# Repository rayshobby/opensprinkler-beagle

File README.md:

opensprinkler-beagle
====================

OpenSprinkler Beagle (http://beagle.opensprinkler.com)

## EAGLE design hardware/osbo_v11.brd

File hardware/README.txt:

OpenSprinkler Beagle (OSBo) Eagle Design Files
==========================================
Note: requires Eagle CAD v6.0 or above

Part lists of all versions can be found at:
http://xxx

Release Notes
=============
Version 1.1
---------------------
- Changed to use OpenSprinkler injection-molded enclosure
- Changed relay to HK4100F-5V

Initial Release v1.0
---------------------
- LM2596S-5.0 switching regulator.
- DS1307 RTC with CR1220 backup battery.
- Shift register, BT1308W triac solenoid driver.
- SMBJ48CA bidirectional TVS.
- 5V mini-relay (contact rating 120VAC/2A).
- 2A solder-on fuse.

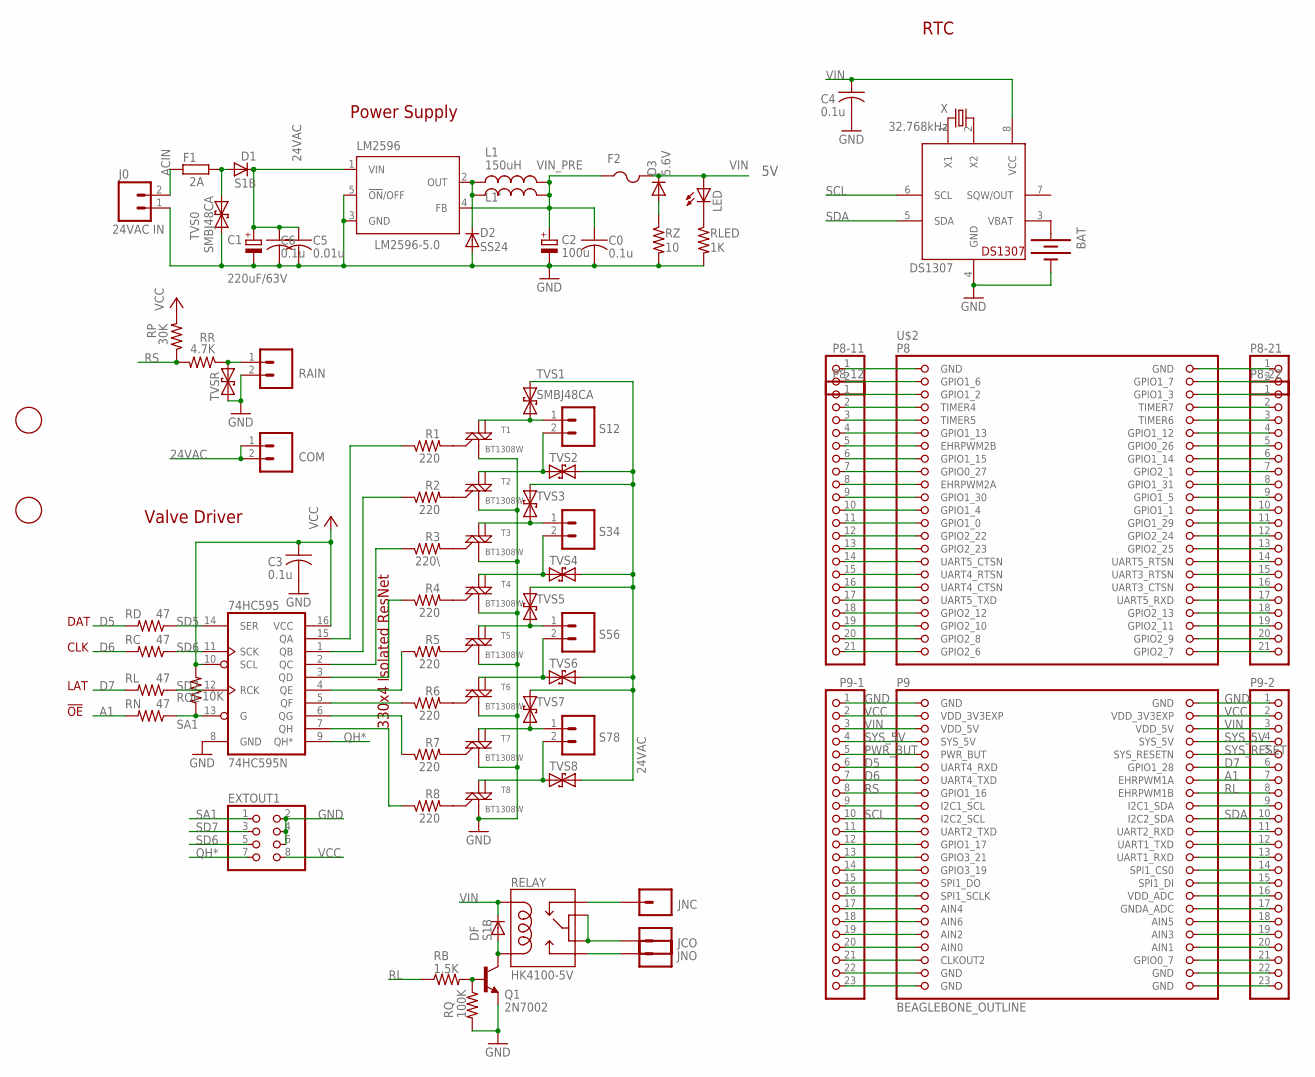
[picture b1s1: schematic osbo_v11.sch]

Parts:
74HC595: 74HC595N; SO16
BAT: BATTERYBATTERY_12MM_SMT; BATTCON_12MM_SMT
C0, C3, C4, C6: 0.1u; C0805K
C1: 220uF/63V; E5-10.5-1
C2: 100u; E3,5-8
C5: 0.01u; C0805K
COM: M025MM-X; SCREWTERMINAL-5MM-2-X
D1: S1B; DO-214AC
D2: SS24; SMB
D3: 5.6V; MINIMELF
DF: S1B; DO-214AC
DS1307: DS1307; SO08
EXTOUT1: PINHD-2X4/90; 2X04/90
F1: 2A; 0411V
F2: PTCFUSE-1812; 1812
J0: 24VAC IN; SCREWTERMINAL-4MM-2-X
JCO: M01PTH; 1X01
JNC: M01PTH; 1X01
JNO: M01PTH; 1X01
L1: 150uH; CDRH125
L1': 150uH; 0207/7
LED: LEDCHIPLED_0805; CHIPLED_0805
LM2596: LM2596-5.0; TO263-5
P8-11, P8-21: PINHD-1X2; 1X02
P8-12, P8-22: PINHD-1X21; 1X21
P9-1, P9-2: PINHD-1X23; 1X23
Q1: 2N7002; SOT23-3
R1, R2, R4, R5, R6, R7, R8: 220; R0805
R3: 220\; R0805
RAIN: M025MM-X; SCREWTERMINAL-5MM-2-X
RB: 1.5K; R0805
RC: 47; R0805
RD: 47; R0805
RELAY: HK4100-5V; RELAY-HK4100F
RL: 47; R0805
RLED: 1K; R0805
RN: 47; R0805
ROE: 10K; R0805
RP: 30K; R0805
RQ: 100K; R0805
RR: 4.7K; R0805
RZ: 10; R0805
S12, S34, S56, S78: M025MM-X; SCREWTERMINAL-5MM-2-X
T1, T2, T3, T4, T5, T6, T7, T8: BT1308W; SOT223
TVS0, TVS1: SMBJ48CA; SMB
TVS2, TVS3, TVS4, TVS5, TVS6, TVS7, TVS8: TVSSMB; SMB
TVSR: TVSSMB; SMB
U$1, U$3: FIDUCIAL; FIDUCIAL_1MM
U$2: BEAGLEBONE_OUTLINE; BEAGLEBONE_SHIELD
X: 32.768kHz; TC38H

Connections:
24VAC: COM.1, COM.2, D1.A, F1.2, TVS0.C, TVS1.C, TVS2.C, TVS3.C, TVS4.C, TVS5.C, TVS6.C, TVS7.C, TVS8.C
A1: P9-2.7, RN.2, U$2.60 (EHRPWM1A)
ACIN: F1.1, J0.2
CO: JCO.1, RELAY.5, RELAY.6
D5: P9-1.6, RD.2, U$2.57 (UART4_RXD)
D6: P9-1.7, RC.2, U$2.59 (UART4_TXD)
D7: P9-2.6, RL.2, U$2.58 (GPIO1_28)
GND: 74HC595.8 (GND), BAT.P$1 (-), C0.2, C1.-, C2.-, C3.2, C4.2, C5.2, C6.2, D2.A, DS1307.4 (GND), EXTOUT1.2, EXTOUT1.4, EXTOUT1.6, J0.1, LM2596.3 (GND), LM2596.5 (!ON!/OFF), P8-11.1, P8-21.1, P9-1.1, P9-2.1, Q1.2 (E), RAIN.2, RLED.2, RQ.2, RZ.2, T1.1 (M1), T2.1 (M1), T3.1 (M1), T4.1 (M1), T5.1 (M1), T6.1 (M1), T7.1 (M1), T8.1 (M1), TVS0.A, TVSR.A, U$2.1 (GND), U$2.2 (GND), U$2.47 (GND), U$2.48 (GND)
unnamed: LED.C, RLED.1
unnamed: C1.+, C5.1, C6.1, D1.C, LM2596.1 (VIN)
unnamed: R1.2, T1.3 (G)
unnamed: 74HC595.5 (QF), R6.1
unnamed: 74HC595.6 (QG), R7.1
unnamed: D3.A, RZ.1
unnamed: 74HC595.7 (QH), R8.1
unnamed: D2.C, L1.1, L1'.1, LM2596.2 (OUT)
unnamed: DS1307.1 (X1), X.2
unnamed: 74HC595.4 (QE), R5.1
unnamed: 74HC595.3 (QD), R4.1
unnamed: 74HC595.2 (QC), R3.1
unnamed: 74HC595.1 (QB), R2.1
unnamed: 74HC595.15 (QA), R1.1
unnamed: R2.2, T2.3 (G)
unnamed: S12.1, T1.2 (M2), TVS1.A
unnamed: S12.2, T2.2 (M2), TVS2.A
unnamed: S34.1, T3.2 (M2), TVS3.A
unnamed: R3.2, T3.3 (G)
unnamed: S34.2, T4.2 (M2), TVS4.A
unnamed: R4.2, T4.3 (G)
unnamed: S56.1, T5.2 (M2), TVS5.A
unnamed: S56.2, T6.2 (M2), TVS6.A
unnamed: S78.1, T7.2 (M2), TVS7.A
unnamed: S78.2, T8.2 (M2), TVS8.A
unnamed: R5.2, T5.3 (G)
unnamed: R6.2, T6.3 (G)
unnamed: R7.2, T7.3 (G)
unnamed: R8.2, T8.3 (G)
unnamed: DS1307.2 (X2), X.1
unnamed: RAIN.1, RR.1, TVSR.C
unnamed: Q1.1 (B), RB.2, RQ.1
unnamed: P8-11.2, U$2.3 (GPIO1_6)
unnamed: P8-12.1, U$2.5 (GPIO1_2)
unnamed: BAT.P$2 (+), DS1307.3 (VBAT)
unnamed: P8-12.2, U$2.7 (TIMER4)
unnamed: P8-12.3, U$2.9 (TIMER5)
unnamed: P8-12.4, U$2.11 (GPIO1_13)
unnamed: P8-12.5, U$2.13 (EHRPWM2B)
unnamed: P8-12.6, U$2.15 (GPIO1_15)
unnamed: P8-12.7, U$2.17 (GPIO0_27)
unnamed: P8-12.8, U$2.19 (EHRPWM2A)
unnamed: P8-12.9, U$2.21 (GPIO1_30)
unnamed: P8-12.10, U$2.23 (GPIO1_4)
unnamed: P8-12.11, U$2.25 (GPIO1_0)
unnamed: P8-12.12, U$2.27 (GPIO2_22)
unnamed: P8-12.13, U$2.29 (GPIO2_23)
unnamed: P8-12.14, U$2.31 (UART5_CTSN)
unnamed: P8-12.15, U$2.33 (UART4_RTSN)
unnamed: P8-12.16, U$2.35 (UART4_CTSN)
unnamed: P8-12.17, U$2.37 (UART5_TXD)
unnamed: P8-12.18, U$2.39 (GPIO2_12)
unnamed: P8-12.19, U$2.41 (GPIO2_10)
unnamed: P8-12.20, U$2.43 (GPIO2_8)
unnamed: P8-12.21, U$2.45 (GPIO2_6)
unnamed: P8-21.2, U$2.4 (GPIO1_7)
unnamed: P8-22.1, U$2.6 (GPIO1_3)
unnamed: P8-22.2, U$2.8 (TIMER7)
unnamed: P8-22.3, U$2.10 (TIMER6)
unnamed: P8-22.4, U$2.12 (GPIO1_12)
unnamed: P8-22.5, U$2.14 (GPIO0_26)
unnamed: P8-22.6, U$2.16 (GPIO1_14)
unnamed: P8-22.7, U$2.18 (GPIO2_1)
unnamed: P8-22.8, U$2.20 (GPIO1_31)
unnamed: P8-22.9, U$2.22 (GPIO1_5)
unnamed: P8-22.10, U$2.24 (GPIO1_1)
unnamed: P8-22.11, U$2.26 (GPIO1_29)
unnamed: P8-22.12, U$2.28 (GPIO2_24)
unnamed: P8-22.13, U$2.30 (GPIO2_25)
unnamed: P8-22.14, U$2.32 (UART5_RTSN)
unnamed: P8-22.15, U$2.34 (UART3_RTSN)
unnamed: P8-22.16, U$2.36 (UART3_CTSN)
unnamed: P8-22.17, U$2.38 (UART5_RXD)
unnamed: P8-22.18, U$2.40 (GPIO2_13)
unnamed: DF.A, Q1.3 (C), RELAY.9
unnamed: P8-22.19, U$2.42 (GPIO2_11)
unnamed: P8-22.20, U$2.44 (GPIO2_9)
unnamed: P8-22.21, U$2.46 (GPIO2_7)
unnamed: P9-1.9, U$2.63 (I2C1_SCL)
unnamed: P9-1.11, U$2.67 (UART2_TXD)
unnamed: P9-1.12, U$2.69 (GPIO1_17)
unnamed: P9-1.13, U$2.71 (GPIO3_21)
unnamed: P9-1.14, U$2.73 (GPIO3_19)
unnamed: P9-1.15, U$2.75 (SPI1_DO)
unnamed: P9-1.16, U$2.77 (SPI1_SCLK)
unnamed: P9-1.17, U$2.79 (AIN4)
unnamed: P9-1.18, U$2.81 (AIN6)
unnamed: P9-1.19, U$2.83 (AIN2)
unnamed: P9-1.20, U$2.85 (AIN0)
unnamed: P9-1.21, U$2.87 (CLKOUT2)
unnamed: P9-1.22, U$2.89 (GND)
unnamed: P9-1.23, U$2.91 (GND)
unnamed: P9-2.9, U$2.64 (I2C1_SDA)
unnamed: P9-2.11, U$2.68 (UART2_RXD)
unnamed: P9-2.12, U$2.70 (UART1_TXD)
unnamed: P9-2.13, U$2.72 (UART1_RXD)
unnamed: P9-2.14, U$2.74 (SPI1_CS0)
unnamed: P9-2.15, U$2.76 (SPI1_DI)
unnamed: P9-2.16, U$2.78 (VDD_ADC)
unnamed: P9-2.17, U$2.80 (GNDA_ADC)
unnamed: P9-2.18, U$2.82 (AIN5)
unnamed: P9-2.19, U$2.84 (AIN3)
unnamed: P9-2.20, U$2.86 (AIN1)
unnamed: P9-2.21, U$2.88 (GPIO0_7)
unnamed: P9-2.22, U$2.90 (GND)
unnamed: P9-2.23, U$2.92 (GND)
NC: JNC.1, RELAY.1
NO: JNO.1, RELAY.10
PWR_BUT: P9-1.5, U$2.55 (PWR_BUT)
QH*: 74HC595.9 (QH*), EXTOUT1.7
RL: P9-2.8, RB.1, U$2.62 (EHRPWM1B)
RS: P9-1.8, RP.1, RR.2, U$2.61 (GPIO1_16)
SA1: 74HC595.13 (G), EXTOUT1.1, RN.1, ROE.1
SCL: DS1307.6 (SCL), P9-1.10, U$2.65 (I2C2_SCL)
SD5: 74HC595.14 (SER), RD.1
SD6: 74HC595.11 (SCK), EXTOUT1.5, RC.1
SD7: 74HC595.12 (RCK), EXTOUT1.3, RL.1
SDA: DS1307.5 (SDA), P9-2.10, U$2.66 (I2C2_SDA)
SYS_5V: P9-1.4, P9-2.4, U$2.53 (SYS_5V), U$2.54 (SYS_5V)
SYS_RESET: P9-2.5, U$2.56 (SYS_RESETN)
VCC: 74HC595.10 (SCL), 74HC595.16 (VCC), C3.1, EXTOUT1.8, P9-1.2, P9-2.2, ROE.2, RP.2, U$2.49 (VDD_3V3EXP), U$2.50 (VDD_3V3EXP)
VIN: C4.1, D3.C, DF.C, DS1307.8 (VCC), F2.2, LED.A, P9-1.3, P9-2.3, RELAY.2, U$2.51 (VDD_5V), U$2.52 (VDD_5V)
VIN_PRE: C0.1, C2.+, F2.1, L1.2, L1'.2, LM2596.4 (FB)

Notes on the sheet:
Power Supply
Valve Driver
DAT
CLK
LAT
330x4 Isolated ResNet
!OE
RTC

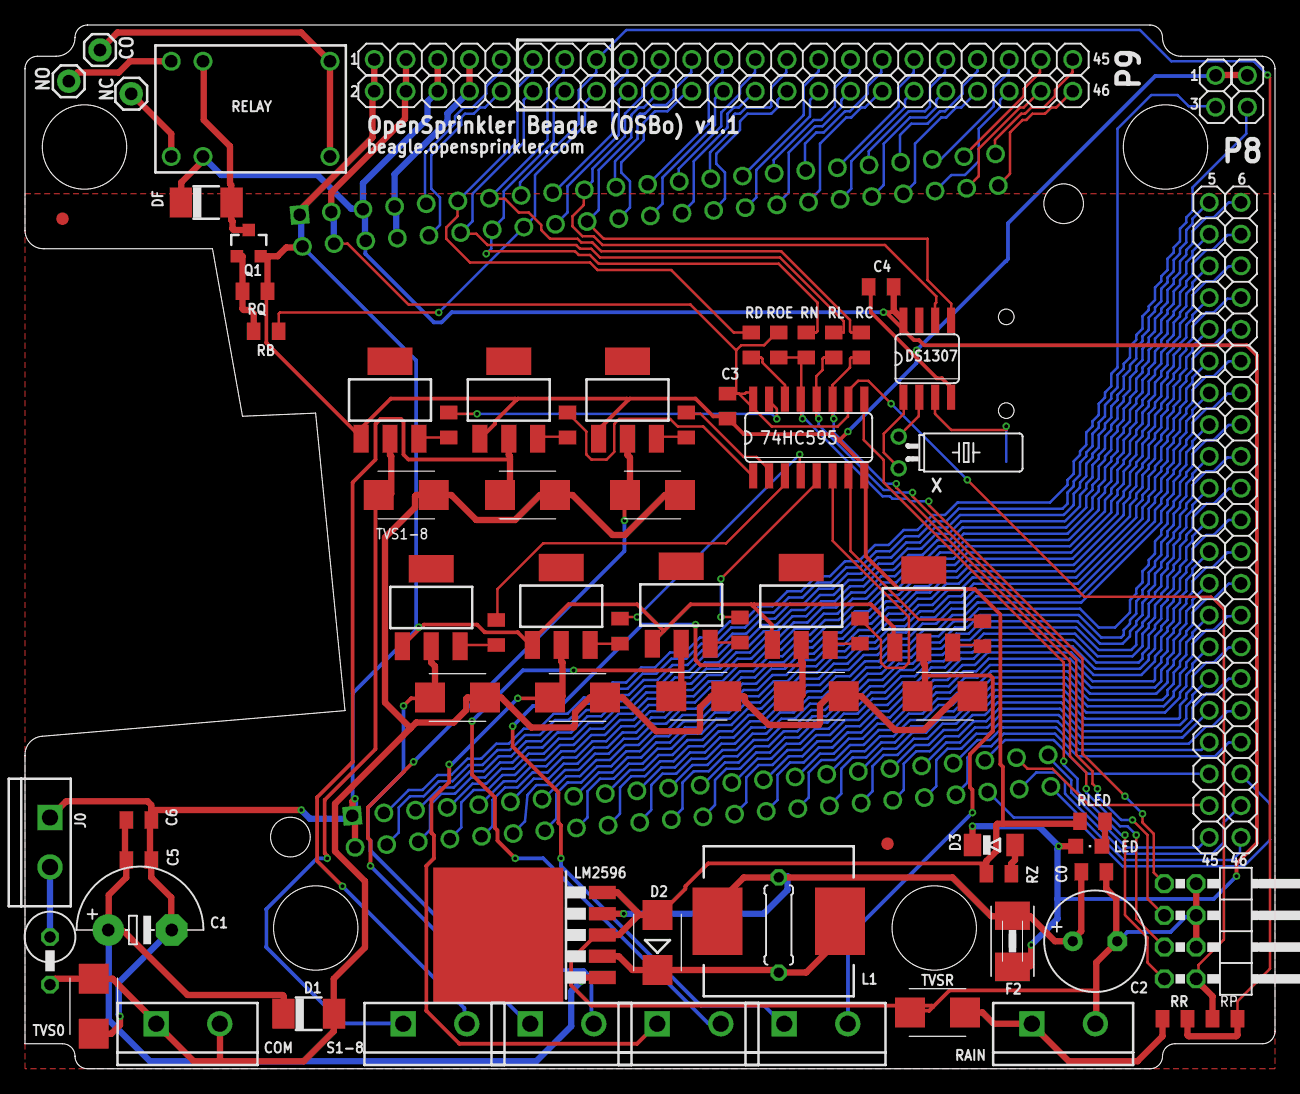
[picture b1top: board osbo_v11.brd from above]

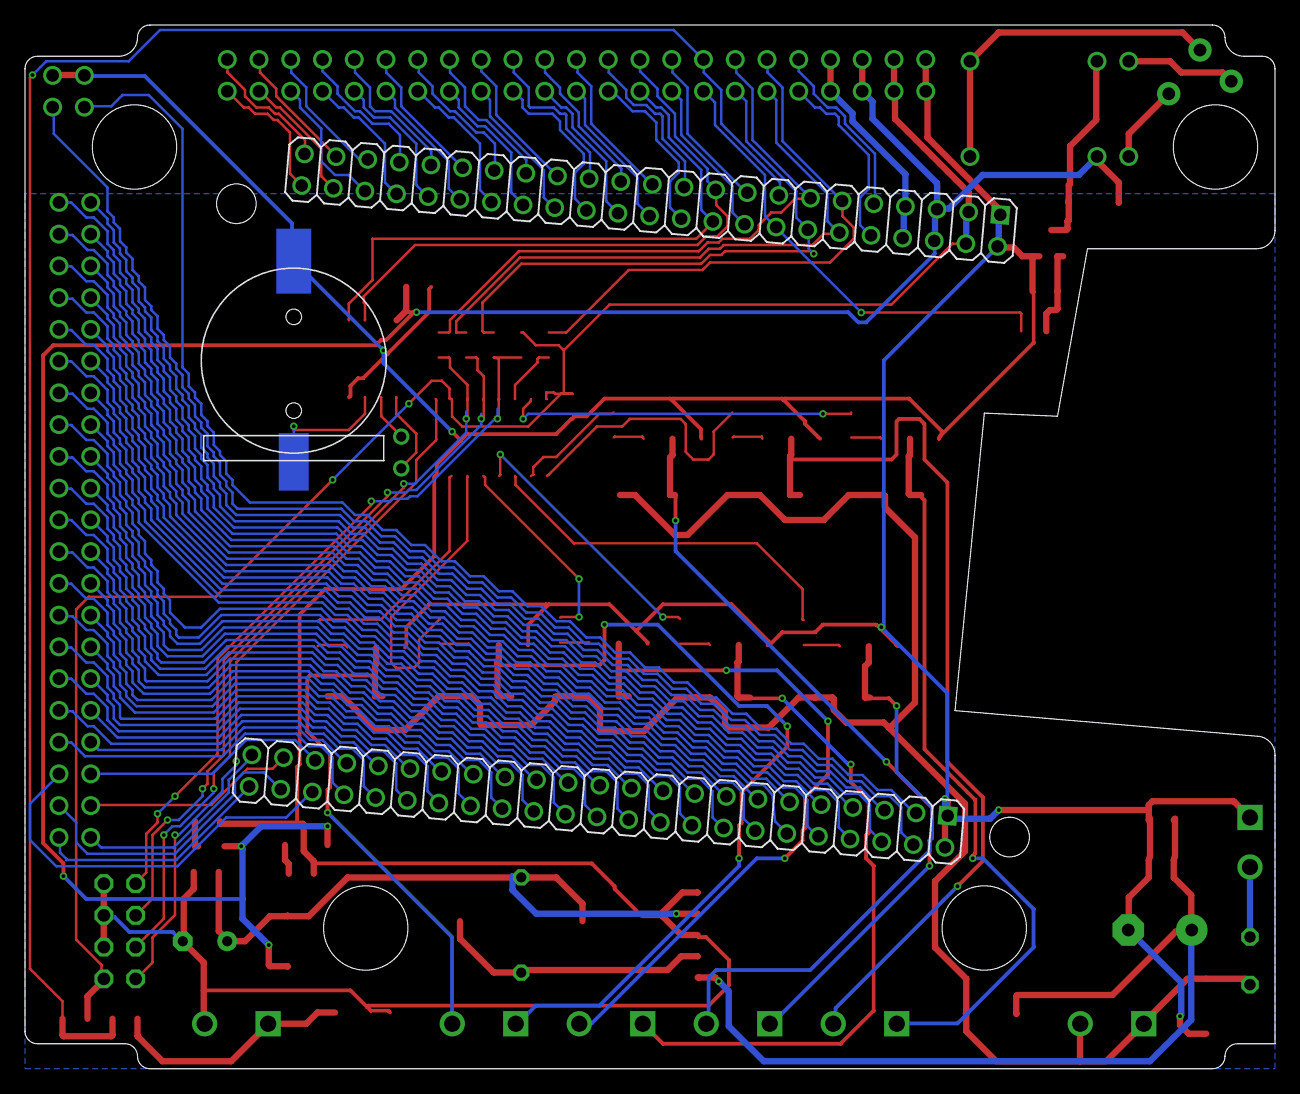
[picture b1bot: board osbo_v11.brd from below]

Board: 2 copper layers, 100.0 x 83.5 mm, 80 parts (2 on the bottom side), 131 nets.

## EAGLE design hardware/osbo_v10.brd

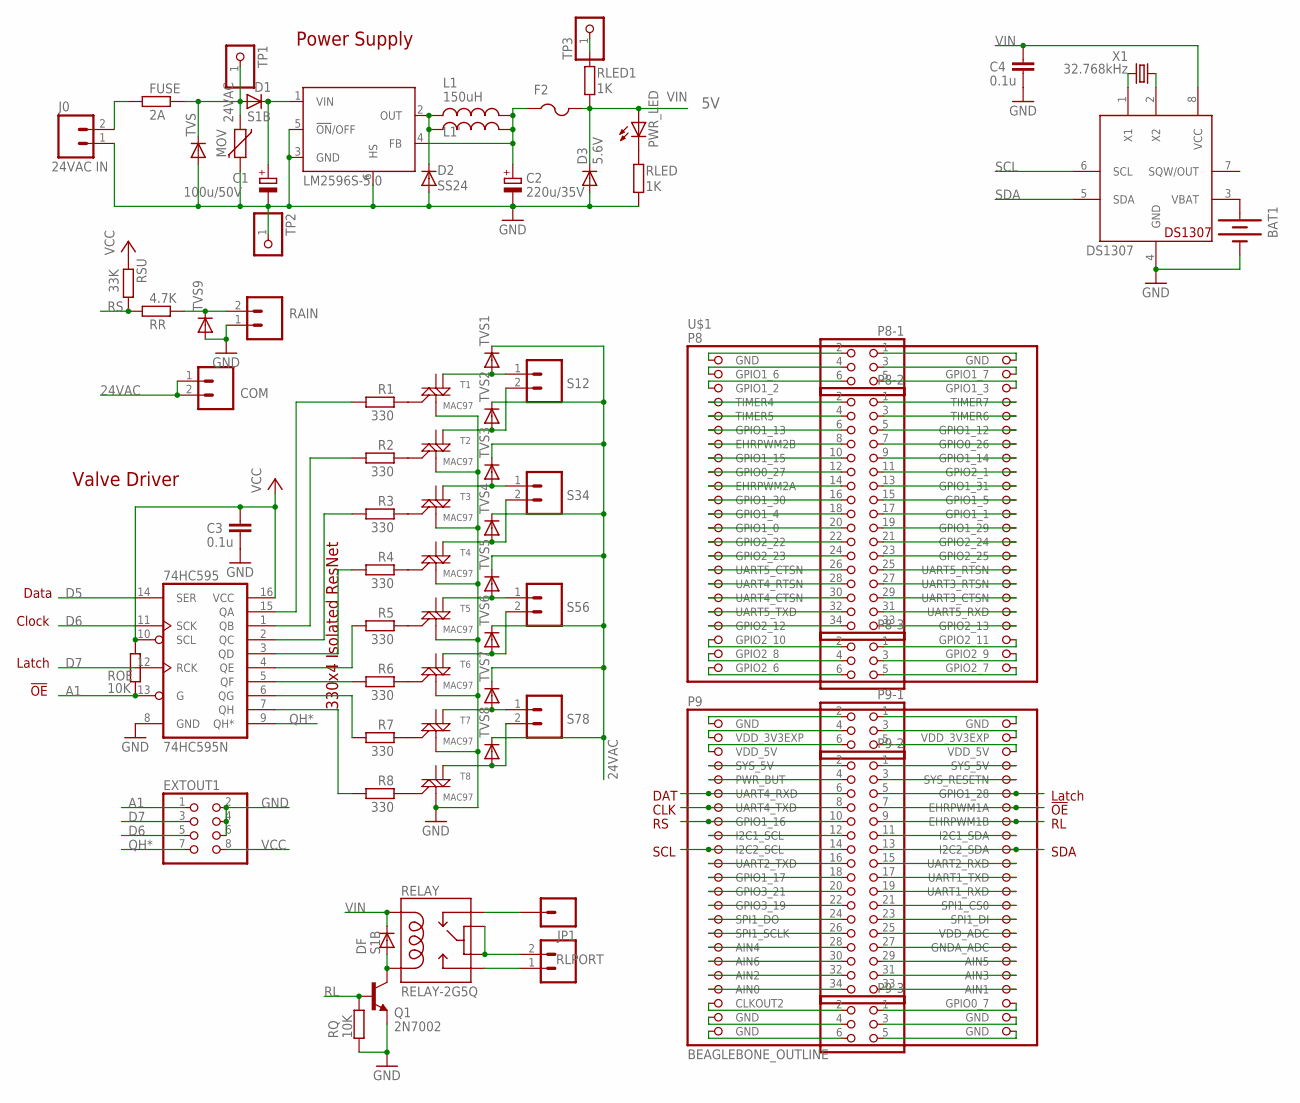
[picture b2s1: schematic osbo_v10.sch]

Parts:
74HC595: 74HC595N; SO16
BAT1: BATTERYBATTERY_12MM_SMT; BATTCON_12MM_SMT
C1: 100u/50V; PANASONIC_E
C2: 220u/35V; PANASONIC_E
C3, C4: 0.1u; C0805
COM: M025MM-X; SCREWTERMINAL-5MM-2-X
D1: S1B; DO-214AC
D2: SS24; SMB
D3: 5.6V; MINIMELF
DF: S1B; DO-214AC
DS1307: DS1307; SO08
EXTOUT1: PINHD-2X4/90; 2X04/90
F2: PTCFUSE-1812; 1812
FUSE: 2A; 0411/15
IC1: LM2596S-5.0; TO263-5
J0: 24VAC IN; SCREWTERMINAL-4MM-2-X
JP1: M01PTH; 1X01
L1: 150uH; CDRH125
L1': 150uH; 0207/7
MOV: VARISTOR-5; R-5
P8-1, P8-3, P9-1, P9-3: PINHD-2X3; 2X03
P8-2, P9-2: PINHD-2X17; 2X17
PWR_LED: LEDCHIPLED_0805; CHIPLED_0805
Q1: 2N7002; SOT23-3
R1, R2, R3, R4, R5, R6, R7, R8: 330; R0805
RAIN: M025MM-X; SCREWTERMINAL-5MM-2-X
RELAY: RELAY-2G5Q; RELAY-G5V
RLED, RLED1: 1K; R0805
RLPORT: M025MM; SCREWTERMINAL-5MM-2
ROE: 10K; R0805
RQ: 10K; R0805
RR: 4.7K; R0805
RSU: 33K; R0805
S12, S34, S56, S78: M025MM-X; SCREWTERMINAL-5MM-2-X
T1, T2, T3, T4, T5, T6, T7, T8: MAC97; SOT223
TP1, TP2, TP3: PINHD-1X1CB; 1X01-CLEANBIG
TVS, TVS1, TVS2, TVS3, TVS4, TVS5, TVS6, TVS7, TVS8, TVS9: DIODE-SMB; SMB
U$1: BEAGLEBONE_OUTLINE; BEAGLEBONE_SHIELD
X1: 32.768kHz; MM20SS

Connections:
24VAC: COM.1, COM.2, D1.A, FUSE.2, MOV.1, TP1.1, TVS.C, TVS1.C, TVS2.C, TVS3.C, TVS4.C, TVS5.C, TVS6.C, TVS7.C, TVS8.C
A1: 74HC595.13 (G), EXTOUT1.1, P9-2.7, ROE.1, U$1.60 (EHRPWM1A)
ACIN: FUSE.1, J0.2
CO: RELAY.5, RELAY.6, RLPORT.2
D5: 74HC595.14 (SER), P9-2.6, U$1.57 (UART4_RXD)
D6: 74HC595.11 (SCK), EXTOUT1.5, P9-2.8, U$1.59 (UART4_TXD)
D7: 74HC595.12 (RCK), EXTOUT1.3, P9-2.5, U$1.58 (GPIO1_28)
G5: R5.2, T5.3 (G)
GND: 74HC595.8 (GND), BAT1.P$1 (-), C1.-, C2.-, C3.2, C4.2, D2.A, D3.A, DS1307.4 (GND), EXTOUT1.2, EXTOUT1.4, EXTOUT1.6, IC1.3 (GND), IC1.5 (!ON!/OFF), IC1.6 (HS), J0.1, MOV.2, P9-1.1, P9-1.2, Q1.2 (E), RAIN.1, RLED.2, RQ.2, T1.1 (M1), T2.1 (M1), T3.1 (M1), T4.1 (M1), T5.1 (M1), T6.1 (M1), T7.1 (M1), T8.1 (M1), TP2.1, TVS.A, TVS9.A, U$1.47 (GND), U$1.48 (GND)
I2C1_SCL: P9-2.12, U$1.63 (I2C1_SCL)
I2C1_SDA: P9-2.11, U$1.64 (I2C1_SDA)
unnamed: PWR_LED.C, RLED.1
unnamed: C1.+, D1.C, IC1.1 (VIN)
unnamed: R1.2, T1.3 (G)
unnamed: 74HC595.5 (QF), R6.1
unnamed: 74HC595.6 (QG), R7.1
unnamed: BAT1.P$2 (+), DS1307.3 (VBAT)
unnamed: 74HC595.7 (QH), R8.1
unnamed: D2.C, IC1.2 (OUT), L1.1, L1'.1
unnamed: P8-1.2, U$1.1 (GND)
unnamed: 74HC595.4 (QE), R5.1
unnamed: 74HC595.3 (QD), R4.1
unnamed: 74HC595.2 (QC), R3.1
unnamed: 74HC595.1 (QB), R2.1
unnamed: 74HC595.15 (QA), R1.1
unnamed: R2.2, T2.3 (G)
unnamed: S12.1, T1.4 (M2-4), TVS1.A
unnamed: S12.2, T2.4 (M2-4), TVS2.A
unnamed: S34.1, T3.4 (M2-4), TVS3.A
unnamed: R3.2, T3.3 (G)
unnamed: S34.2, T4.4 (M2-4), TVS4.A
unnamed: R4.2, T4.3 (G)
unnamed: S56.1, T5.4 (M2-4), TVS5.A
unnamed: S56.2, T6.4 (M2-4), TVS6.A
unnamed: S78.1, T7.4 (M2-4), TVS7.A
unnamed: S78.2, T8.4 (M2-4), TVS8.A
unnamed: RAIN.2, RR.1, TVS9.C
unnamed: R6.2, T6.3 (G)
unnamed: R7.2, T7.3 (G)
unnamed: R8.2, T8.3 (G)
unnamed: P8-1.1, U$1.2 (GND)
unnamed: DS1307.1 (X1), X1.1
unnamed: P8-1.4, U$1.3 (GPIO1_6)
unnamed: P8-1.3, U$1.4 (GPIO1_7)
unnamed: P8-1.6, U$1.5 (GPIO1_2)
unnamed: P8-1.5, U$1.6 (GPIO1_3)
unnamed: P8-3.6, U$1.45 (GPIO2_6)
unnamed: P8-3.5, U$1.46 (GPIO2_7)
unnamed: P8-3.4, U$1.43 (GPIO2_8)
unnamed: P8-3.2, U$1.41 (GPIO2_10)
unnamed: P8-3.3, U$1.44 (GPIO2_9)
unnamed: P8-3.1, U$1.42 (GPIO2_11)
unnamed: P8-2.2, U$1.7 (TIMER4)
unnamed: P8-2.4, U$1.9 (TIMER5)
unnamed: P8-2.6, U$1.11 (GPIO1_13)
unnamed: P8-2.8, U$1.13 (EHRPWM2B)
unnamed: P8-2.10, U$1.15 (GPIO1_15)
unnamed: P8-2.12, U$1.17 (GPIO0_27)
unnamed: P8-2.14, U$1.19 (EHRPWM2A)
unnamed: P8-2.16, U$1.21 (GPIO1_30)
unnamed: P8-2.18, U$1.23 (GPIO1_4)
unnamed: P8-2.20, U$1.25 (GPIO1_0)
unnamed: P8-2.22, U$1.27 (GPIO2_22)
unnamed: P8-2.24, U$1.29 (GPIO2_23)
unnamed: P8-2.26, U$1.31 (UART5_CTSN)
unnamed: P8-2.28, U$1.33 (UART4_RTSN)
unnamed: P8-2.30, U$1.35 (UART4_CTSN)
unnamed: P8-2.32, U$1.37 (UART5_TXD)
unnamed: P8-2.34, U$1.39 (GPIO2_12)
unnamed: P8-2.1, U$1.8 (TIMER7)
unnamed: P8-2.3, U$1.10 (TIMER6)
unnamed: P8-2.5, U$1.12 (GPIO1_12)
unnamed: P8-2.7, U$1.14 (GPIO0_26)
unnamed: P8-2.9, U$1.16 (GPIO1_14)
unnamed: P8-2.11, U$1.18 (GPIO2_1)
unnamed: P8-2.13, U$1.20 (GPIO1_31)
unnamed: P8-2.15, U$1.22 (GPIO1_5)
unnamed: P8-2.17, U$1.24 (GPIO1_1)
unnamed: P8-2.19, U$1.26 (GPIO1_29)
unnamed: P8-2.21, U$1.28 (GPIO2_24)
unnamed: P8-2.23, U$1.30 (GPIO2_25)
unnamed: P8-2.25, U$1.32 (UART5_RTSN)
unnamed: P8-2.27, U$1.34 (UART3_RTSN)
unnamed: P8-2.29, U$1.36 (UART3_CTSN)
unnamed: P8-2.31, U$1.38 (UART5_RXD)
unnamed: P8-2.33, U$1.40 (GPIO2_13)
unnamed: DS1307.2 (X2), X1.4 (2)
unnamed: DF.A, Q1.3 (C), RELAY.9
unnamed: RLED1.1, TP3.1
unnamed: P9-3.6, U$1.91 (GND)
unnamed: P9-3.4, U$1.89 (GND)
unnamed: P9-3.2, U$1.87 (CLKOUT2)
unnamed: P9-3.5, U$1.92 (GND)
unnamed: P9-3.3, U$1.90 (GND)
unnamed: P9-3.1, U$1.88 (GPIO0_7)
unnamed: P9-2.15, U$1.68 (UART2_RXD)
unnamed: P9-2.17, U$1.70 (UART1_TXD)
unnamed: P9-2.19, U$1.72 (UART1_RXD)
unnamed: P9-2.21, U$1.74 (SPI1_CS0)
unnamed: P9-2.23, U$1.76 (SPI1_DI)
unnamed: P9-2.25, U$1.78 (VDD_ADC)
unnamed: P9-2.27, U$1.80 (GNDA_ADC)
unnamed: P9-2.29, U$1.82 (AIN5)
unnamed: P9-2.31, U$1.84 (AIN3)
unnamed: P9-2.33, U$1.86 (AIN1)
unnamed: P9-2.16, U$1.67 (UART2_TXD)
unnamed: P9-2.18, U$1.69 (GPIO1_17)
unnamed: P9-2.20, U$1.71 (GPIO3_21)
unnamed: P9-2.22, U$1.73 (GPIO3_19)
unnamed: P9-2.24, U$1.75 (SPI1_DO)
unnamed: P9-2.26, U$1.77 (SPI1_SCLK)
unnamed: P9-2.28, U$1.79 (AIN4)
unnamed: P9-2.30, U$1.81 (AIN6)
unnamed: P9-2.32, U$1.83 (AIN2)
unnamed: P9-2.34, U$1.85 (AIN0)
NC: JP1.1, RELAY.1
NO: RELAY.10, RLPORT.1
PWR_BUT: P9-2.4, U$1.55 (PWR_BUT)
QH*: 74HC595.9 (QH*), EXTOUT1.7
RL: P9-2.9, Q1.1 (B), RQ.1, U$1.62 (EHRPWM1B)
RS: P9-2.10, RR.2, RSU.1, U$1.61 (GPIO1_16)
SCL: DS1307.6 (SCL), P9-2.14, U$1.65 (I2C2_SCL)
SDA: DS1307.5 (SDA), P9-2.13, U$1.66 (I2C2_SDA)
SYS_5V: P9-2.1, P9-2.2, U$1.53 (SYS_5V), U$1.54 (SYS_5V)
SYS_RESET: P9-2.3, U$1.56 (SYS_RESETN)
VCC: 74HC595.10 (SCL), 74HC595.16 (VCC), C3.1, EXTOUT1.8, P9-1.3, P9-1.4, ROE.2, RSU.2, U$1.49 (VDD_3V3EXP), U$1.50 (VDD_3V3EXP)
VIN: C4.1, D3.C, DF.C, DS1307.8 (VCC), F2.2, P9-1.5, P9-1.6, PWR_LED.A, RELAY.2, RLED1.2, U$1.51 (VDD_5V), U$1.52 (VDD_5V)
VIN_PRE: C2.+, F2.1, IC1.4 (FB), L1.2, L1'.2

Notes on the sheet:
Power Supply
Valve Driver
Data
Clock
Latch
330x4 Isolated ResNet
!OE
DAT
CLK
SCL
SDA

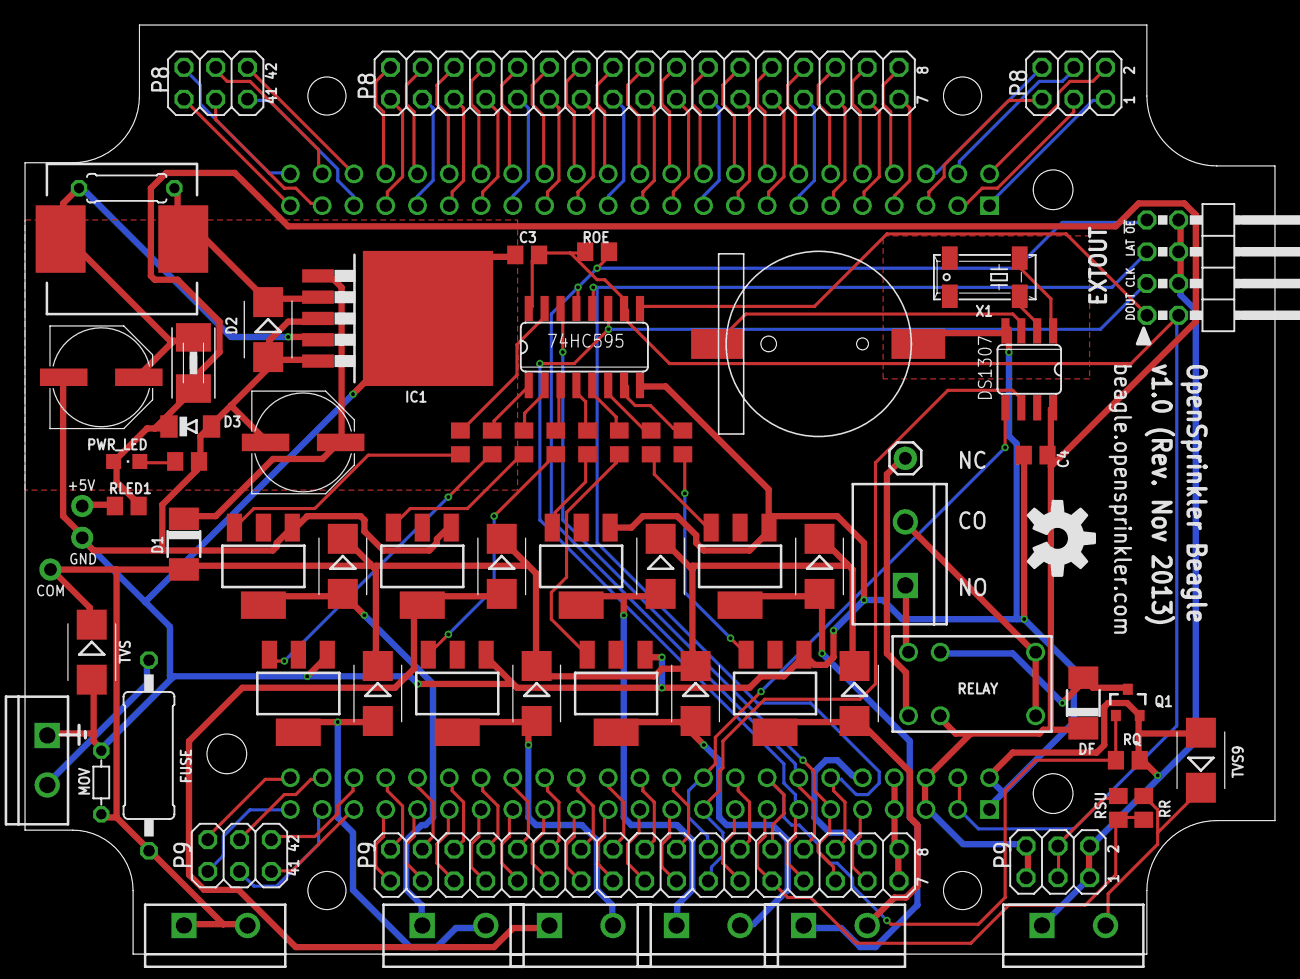
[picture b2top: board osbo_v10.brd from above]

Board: 2 copper layers, 99.9 x 74.3 mm, 73 parts (1 on the bottom side), 128 nets.

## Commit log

2013-11-13 initial checkin of osbo 1.0 hardware files
2013-11-13 minor change to the board design
2013-11-14 check in OSBo v1.0 BOM
2013-11-24 fix bidirectional tvs symbol in the schematic.
2015-04-25 check in OSBo 1.1 Eagle files
